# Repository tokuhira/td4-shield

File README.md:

# td4-shield

「CPUの創りかた」に則ったちょっと最近のプロジェクトです。

# Photo

# Features

書籍に記載の内容を少しアレンジしての製作例です。
汎用ロジックICはSOICにしています。
ROMと電源はArduinoで代用するため、UNO用のShieldとして使います。
コードはArduino全般で動作することを目標としつつも、メインターゲットはSTM32です。

# Requirement

Arduino互換のボードが別途必要です。

# Installation

色々やり方はありますが、Arduino UNOに差し込むのが簡単です。
ボードのIO電圧に合わせてJP1を設定します。

# Usage

各々方でご自由に実験していただけます。

# Note

可用性、安全性、その他いかなる性質も保証しません。
いかなる用法も、またのその結果も保証しません。

# Author

* @tokuhira (twitter)
* github.com/tokuhira

# License

BSD 3-Clause License

Copyright (c) 2020, tokuhira.net
All rights reserved.

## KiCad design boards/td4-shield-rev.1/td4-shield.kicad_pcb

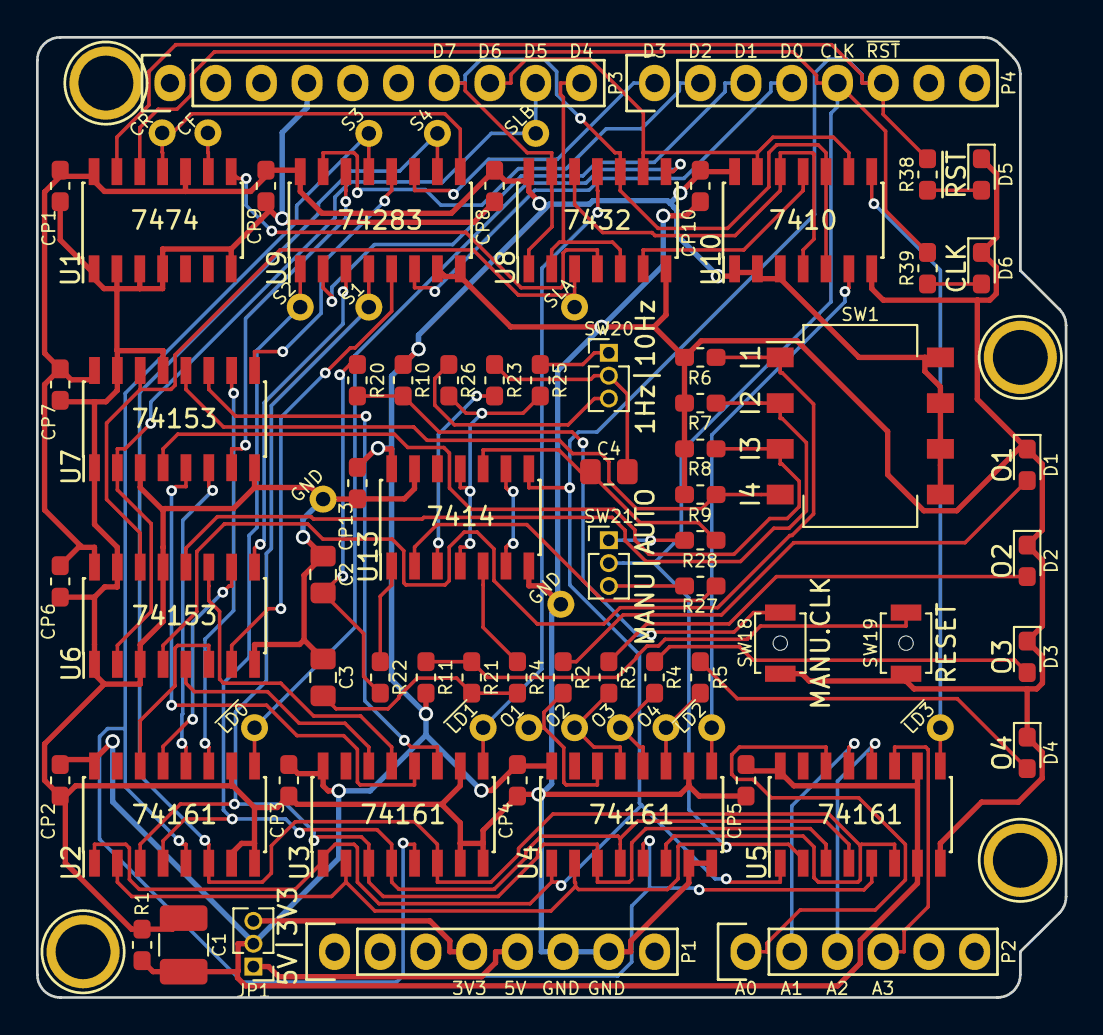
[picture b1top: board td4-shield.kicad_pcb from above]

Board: 2 copper layers, 57.2 x 53.3 mm, 87 parts (1 on the bottom side), 74 nets.

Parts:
C1: 100uF 16V; C_1210_3225Metric_Pad1.42x2.65mm_HandSolder
C2, C3, C4: 10uF 16V; C_0805_2012Metric_Pad1.15x1.40mm_HandSolder
CP1, CP2, CP3, CP4, CP5, CP6, CP7, CP8, CP9, CP10, CP13: 0.1uF; C_0603_1608Metric_Pad1.05x0.95mm_HandSolder
D1, D2, D3, D4, D5, D6: LED; D_0603_1608Metric_Pad1.05x0.95mm_HandSolder
JP1: VCC:+5V/+3V3; PinHeader_1x03_P1.27mm_Vertical
LOGO1: OSHW-Logo2_9.8x8mm_SilkScreen
P1: Power; Socket_Strip_Arduino_1x08
P2: Analog; Socket_Strip_Arduino_1x06
P3: Digital; Socket_Strip_Arduino_1x10
P4: Digital; Socket_Strip_Arduino_1x08
P5, P6, P7, P8: CONN_01X01; Arduino_1pin
R1: DNP; R_0603_1608Metric_Pad1.05x0.95mm_HandSolder
R2, R3, R4, R5, R6, R7, R8, R9, R10, R11, R38, R39: 1K; R_0603_1608Metric_Pad1.05x0.95mm_HandSolder
R20: 10K; R_0603_1608Metric_Pad1.05x0.95mm_HandSolder
R21, R22, R23, R24: 100K; R_0603_1608Metric_Pad1.05x0.95mm_HandSolder
R25: 3.3K; R_0603_1608Metric_Pad1.05x0.95mm_HandSolder
R26: 33K; R_0603_1608Metric_Pad1.05x0.95mm_HandSolder
R27, R28: 100; R_0603_1608Metric_Pad1.05x0.95mm_HandSolder
SW1: INPUT; SW_DIP_SPSTx04_Slide_Omron_A6S-410x_W8.9mm_P2.54mm
SW18: Manual Clock; SW_SPST_B3U-1000P-B
SW19: Reset; SW_SPST_B3U-1000P-B
SW20: CLK:10Hz/1Hz; PinHeader_1x03_P1.27mm_Vertical
SW21: CLK:NOR/MAN; PinHeader_1x03_P1.27mm_Vertical
TP1: S1; Measurement_Point_Round-TH_Small
TP2: S2; Measurement_Point_Round-TH_Small
TP3: S3; Measurement_Point_Round-TH_Small
TP4: S4; Measurement_Point_Round-TH_Small
TP5: CR; Measurement_Point_Round-TH_Small
TP6: CF; Measurement_Point_Round-TH_Small
TP7: LD0; Measurement_Point_Round-TH_Small
TP8: LD1; Measurement_Point_Round-TH_Small
TP9: LD2; Measurement_Point_Round-TH_Small
TP10: LD3; Measurement_Point_Round-TH_Small
TP11: SLA; Measurement_Point_Round-TH_Small
TP12: SLB; Measurement_Point_Round-TH_Small
TP13: O1; Measurement_Point_Round-TH_Small
TP14: O2; Measurement_Point_Round-TH_Small
TP15: O3; Measurement_Point_Round-TH_Small
TP16: O4; Measurement_Point_Round-TH_Small
TP17, TP18: GND; Measurement_Point_Round-TH_Small
U1: 74HC74; SOIC-14_3.9x8.7mm_Pitch1.27mm
U2, U3, U4, U5: 74HC161; SOIC-16_3.9x9.9mm_Pitch1.27mm
U6, U7: 74HC153; SOIC-16_3.9x9.9mm_Pitch1.27mm
U8: 74HC32; SOIC-14_3.9x8.7mm_Pitch1.27mm
U9: 74HC283; SOIC-16_3.9x9.9mm_Pitch1.27mm
U10: 74HC10; SOIC-14_3.9x8.7mm_Pitch1.27mm
U13: 74HC14; SOIC-14_3.9x8.7mm_Pitch1.27mm

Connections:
+3V3: JP1.3, P1.4
+5V: JP1.1, P1.5
/2: P4.6, R38.1, U1.13, U2.1, U3.1, U4.1, U5.1, U13.8
/3(**): P4.5, R39.1, SW21.2, U1.12, U2.2, U3.2, U4.2, U5.2
/ALU_C: TP5.1, U1.11, U9.9
/ALU_S1: TP1.1, U2.3, U3.3, U4.3, U5.3, U9.4
/ALU_S2: TP2.1, U2.4, U3.4, U4.4, U5.4, U9.1
/ALU_S3: TP3.1, U2.5, U3.5, U4.5, U5.5, U9.13
/ALU_S4: TP4.1, U2.6, U3.6, U4.6, U5.6, U9.10
/FLG_C: TP6.1, U1.9
/IN1: R6.1, SW1.1, U6.4
/IN2: R7.1, SW1.2, U6.12
/IN3: R8.1, SW1.3, U7.4
/IN4: R9.1, SW1.4, U7.12
/OUT1: R2.1, TP13.1, U4.14
/OUT2: R3.1, TP14.1, U4.13
/OUT3: R4.1, TP15.1, U4.12
/OUT4: R5.1, TP16.1, U4.11
/RA1: U2.14, U6.6
/RA2: U2.13, U6.10
/RA3: U2.12, U7.6
/RA4: U2.11, U7.10
/RB1: U3.14, U6.5
/RB2: U3.13, U6.11
/RB3: U3.12, U7.5
/RB4: U3.11, U7.11
/SEL_A: TP11.1, U6.14, U7.14, U8.3
/~FLG_C: U1.8, U8.4
/~LOAD0: TP7.1, U2.9, U8.8
/~LOAD1: TP8.1, U3.9, U8.11
/~LOAD2: TP9.1, U4.9, U10.6
/~LOAD3: TP10.1, U5.9, U10.8
GND: C1.2, C2.2, C3.2, CP1.2, CP2.2, CP3.2, CP4.2, CP5.2, CP6.2, CP7.2, CP8.2, CP9.2, CP10.2, CP13.2, D1.1, D2.1, D3.1, D4.1, D5.1, D6.1, P1.6, P1.7, P3.4, R1.2, R6.2, R7.2, R8.2, R9.2, SW18.1, SW19.1, TP17.1, TP18.1, U1.1, U1.2, U1.3, U1.4, U1.7, U2.7, U2.8, U2.10, U3.7, U3.8, U3.10, U4.7, U4.8, U4.10, U5.8, U6.1, U6.3, U6.8, U6.13, U6.15, U7.1, U7.3, U7.8, U7.13, U7.15, U8.7, U9.7, U9.8, U10.7, U13.7, U13.13
unnamed: C2.1, R20.2, R22.1
unnamed: C3.1, R21.2, R24.1
unnamed: C4.1, R28.1, U13.10
unnamed: C4.2, R23.1, SW20.2
unnamed: D1.2, R2.2
unnamed: D2.2, R3.2
unnamed: D3.2, R4.2
unnamed: D4.2, R5.2
unnamed: D5.2, R38.2
unnamed: D6.2, R39.2
unnamed: R10.2, R20.1, SW18.2
unnamed: R11.2, R21.1, SW19.2
unnamed: R22.2, U13.1
unnamed: R23.2, U13.3
unnamed: R24.2, U13.5
unnamed: R25.1, SW20.1
unnamed: R25.2, R26.1, U13.4, U13.11
unnamed: R26.2, SW20.3
unnamed: R27.1, U13.2
unnamed: R27.2, SW21.3
unnamed: R28.2, SW21.1
unnamed: U6.7, U9.5
unnamed: U6.9, U9.3
unnamed: U7.7, U9.14
unnamed: U7.9, U9.12
unnamed: U8.6, U10.11
unnamed: U8.12, U10.4, U10.12
unnamed: U13.6, U13.9
ROM_A0: P2.1, U5.14
ROM_A1: P2.2, U5.13
ROM_A2: P2.3, U5.12
ROM_A3: P2.4, U5.11
ROM_D0: P4.4, U9.6
ROM_D1: P4.3, U9.2
ROM_D2: P4.2, U9.15
ROM_D3: P4.1, U9.11
ROM_D4: P3.10, U8.2, U8.5
ROM_D5: P3.9, TP12.1, U6.2, U7.2
ROM_D6: P3.8, U8.9, U10.9, U10.13
ROM_D7: P3.7, U8.1, U8.10, U8.13, U10.5, U10.10
VCC: C1.1, CP1.1, CP2.1, CP3.1, CP4.1, CP5.1, CP6.1, CP7.1, CP8.1, CP9.1, CP10.1, CP13.1, JP1.2, R1.1, R10.1, R11.1, SW1.5, SW1.6, SW1.7, SW1.8, U1.10, U1.14, U2.16, U3.16, U4.16, U5.7, U5.10, U5.16, U6.16, U7.16, U8.14, U9.16, U10.1, U10.2, U10.3, U10.14, U13.14

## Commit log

2020-08-19 Create td4-shield-rev.1 board
2020-08-20 Update kicad_pcb and gerber
    Silk modified.
2020-08-20 Update README and gitignore
2020-08-20 Update README.md
    Add 3d view image.
2020-08-20 Create "Triaezu Dousa Mikakunin ROM emulator"
2020-08-21 Update td4_iface.h
    Remove the dependency to STM32.
2020-08-22 Upload some resources of rev.0
2020-08-22 Update rom_init_clk
    ROM definition separation.
2020-08-22 Create stm32cube/rom_int_clk for NUCLEO-F030R8
2020-08-24 Update main.c of stm32cube/rom_int_clk
2020-08-27 Update td4-shield.sch
    Bug fix on sch, kicad_pcb has not been fixed yet!
2020-08-28 Fix the bugs on wiring to U2, U3, U4, and U5.
2020-09-07 Update td4-shield-rev.1
    Add BOM and positions.
2020-09-08 Update gerber files
2021-01-10 Update td4-shield-rev.0_parts.pdf
    Fixed the parts no. of SW1 and SW18,SW19 being staggered.
    Fixed omission of description of U6,U7.
2021-01-10 Update td4-shield-rev.0_parts.pdf
    Change the date of the sheet name.
2021-02-04 Update codes with STM32CubeIDE
    STM32CubeIDE version: 1.4.2 -> 1.5.1
    FirmwarePackage: STM32Cube FW_F0 V1.11.0 -> STM32Cube FW_F0 V1.11.2
2021-02-04 Assign pins for I2C (PB8 and PB9)
2021-02-05 Update rom_int_clk with STM32CubeIDE
    Drive 7 segments LED by PCA9624PW with program counter.
2021-02-06 Update rom_int_clk with Adruino
    Drive 7 segments LED by PCA9624PW with program counter.
2021-05-21 Migrate to latest STM32CubeIDE
    STM32CubeIDE
    Version: 1.6.1
    Build: 9958_20210326_1446 (UTC)
